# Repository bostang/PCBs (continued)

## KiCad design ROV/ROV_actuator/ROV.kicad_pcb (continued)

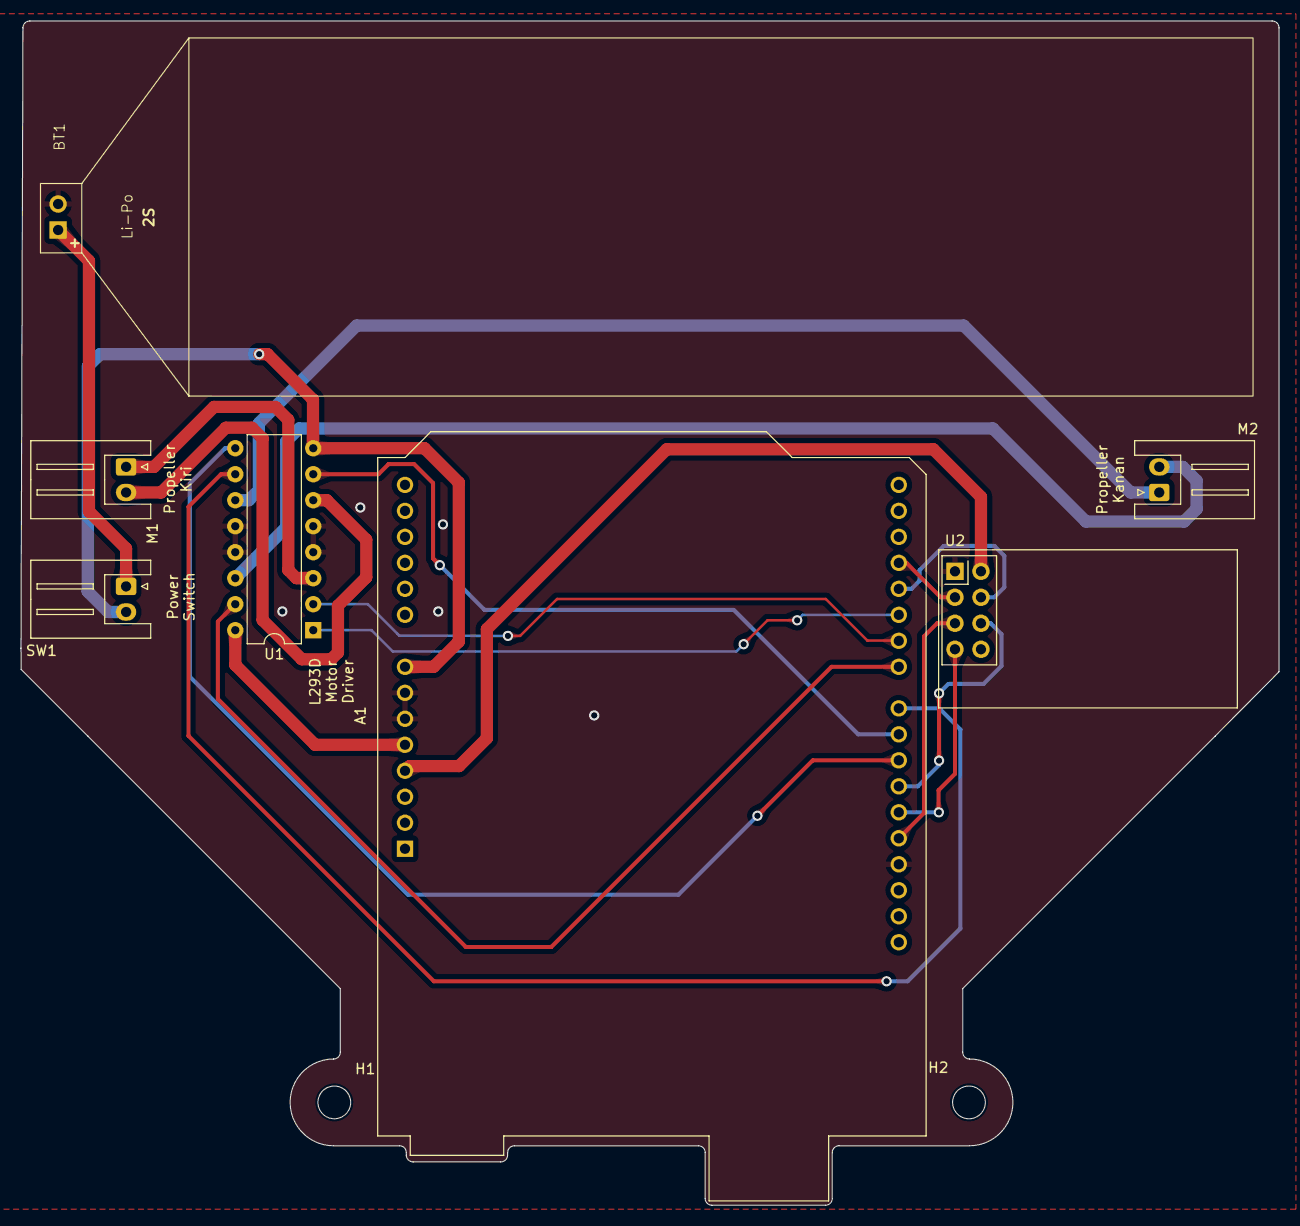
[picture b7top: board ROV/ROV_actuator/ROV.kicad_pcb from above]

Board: 2 copper layers, 123.0 x 115.7 mm, 9 parts (0 on the bottom side), 20 nets.

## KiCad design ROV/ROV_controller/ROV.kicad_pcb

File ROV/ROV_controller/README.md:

# ROV Controller

Rangkaian pengendali untuk robot bawah air

# Skematik

# Tampilan

## Tampak Atas

## Tampak Bawah

## Bird-view

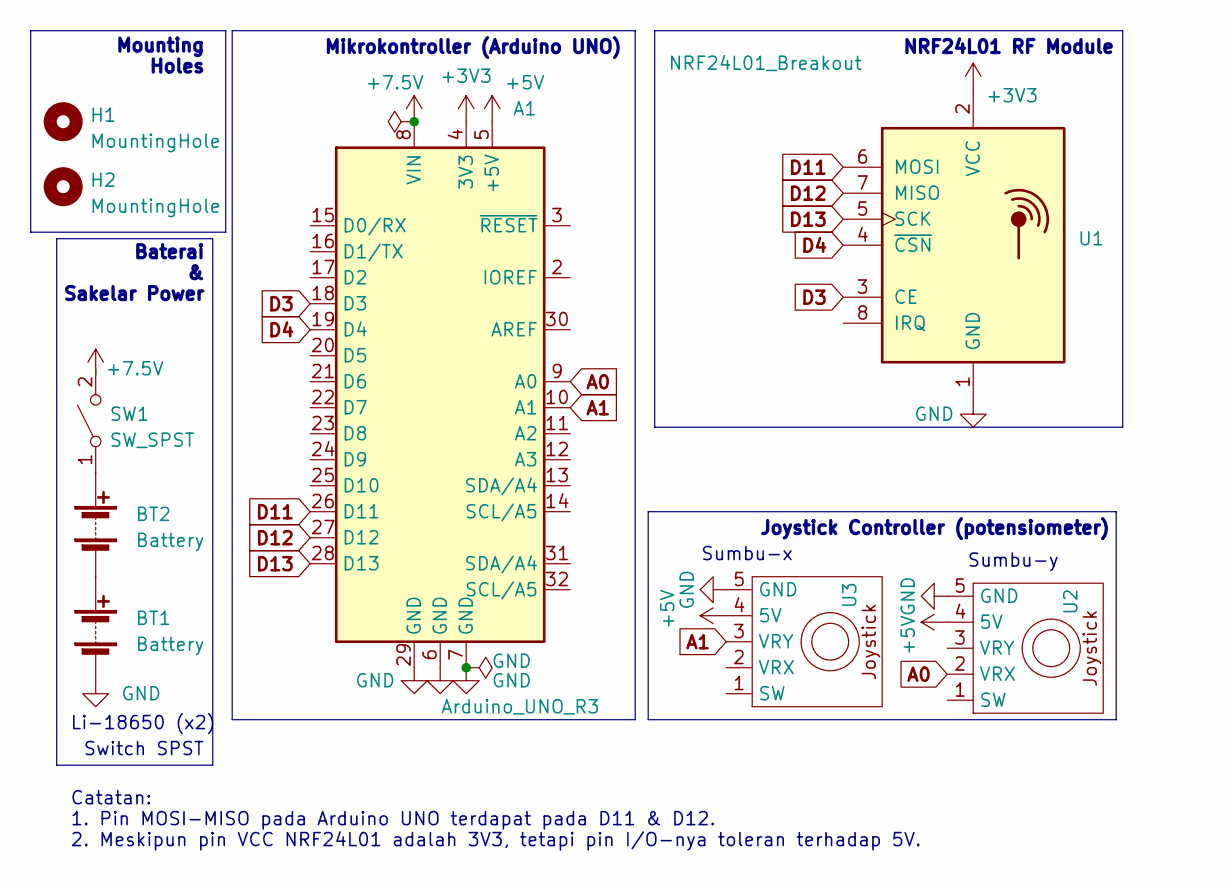
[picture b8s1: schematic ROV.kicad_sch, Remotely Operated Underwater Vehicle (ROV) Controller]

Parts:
A1: Arduino_UNO_R3
BT1, BT2: Battery; BatteryHolder_MPD_BH-18650-PC2
H1, H2: MountingHole; MountingHole_3.2mm_M3
SW1: SW_SPST; JST_XH_S2B-XH-A_1x02_P2.50mm_Horizontal
U1: NRF24L01_Breakout; nRF24L01_Breakout
U2, U3: Joystick Module

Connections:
+3V3: A1.4 (3V3), U1.2 (VCC)
+5V: A1.5 (+5V), U2.4 (5V), U3.4 (5V)
+7.5V: A1.8 (VIN), SW1.2 (B)
A0: A1.9 (A0), U2.2 (VRX)
A1: A1.10 (A1), U3.3 (VRY)
D3: A1.18 (D3), U1.3 (CE)
D4: A1.19 (D4), U1.4 (~CSN)
D11: A1.26 (D11), U1.6 (MOSI)
D12: A1.27 (D12), U1.7 (MISO)
D13: A1.28 (D13), U1.5 (SCK)
GND: A1.6 (GND), A1.7 (GND), A1.29 (GND), BT1.2 (-), U1.1 (GND), U2.5 (GND), U3.5 (GND)
unnamed: BT1.1 (+), BT2.2 (-)
unnamed: BT2.1 (+), SW1.1 (A)

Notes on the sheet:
NRF24L01 RF Module
Sumbu-y
Li-18650 (x2)
Mikrokontroller (Arduino UNO)
Sumbu-x
Joystick Controller (potensiometer)
Mounting Holes
Catatan: 1. Pin MOSI-MISO pada Arduino UNO terdapat pada D11 & D12. 2. Meskipun pin VCC NRF24L01 adalah 3V3, tetapi pin I/O-nya toleran terhadap 5V.
Switch SPST
Baterai & Sakelar Power

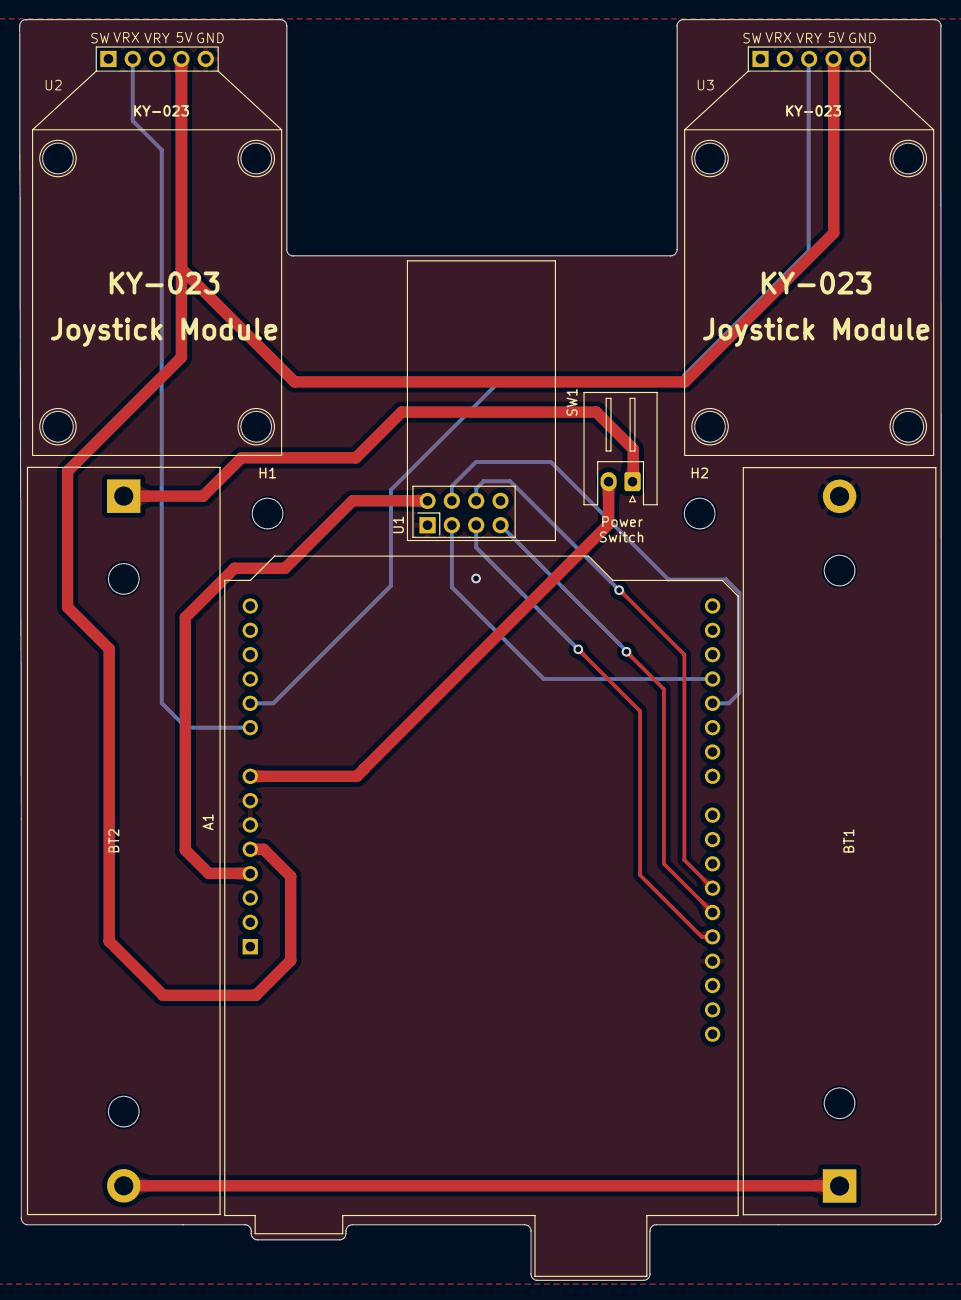
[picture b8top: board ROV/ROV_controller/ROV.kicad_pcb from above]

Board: 2 copper layers, 96.2 x 131.6 mm, 9 parts (0 on the bottom side), 13 nets.
